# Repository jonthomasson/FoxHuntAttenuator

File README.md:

# FoxHuntAttenuator
Adjustable Pi Attenuator network that aids in ham radio fox hunting.

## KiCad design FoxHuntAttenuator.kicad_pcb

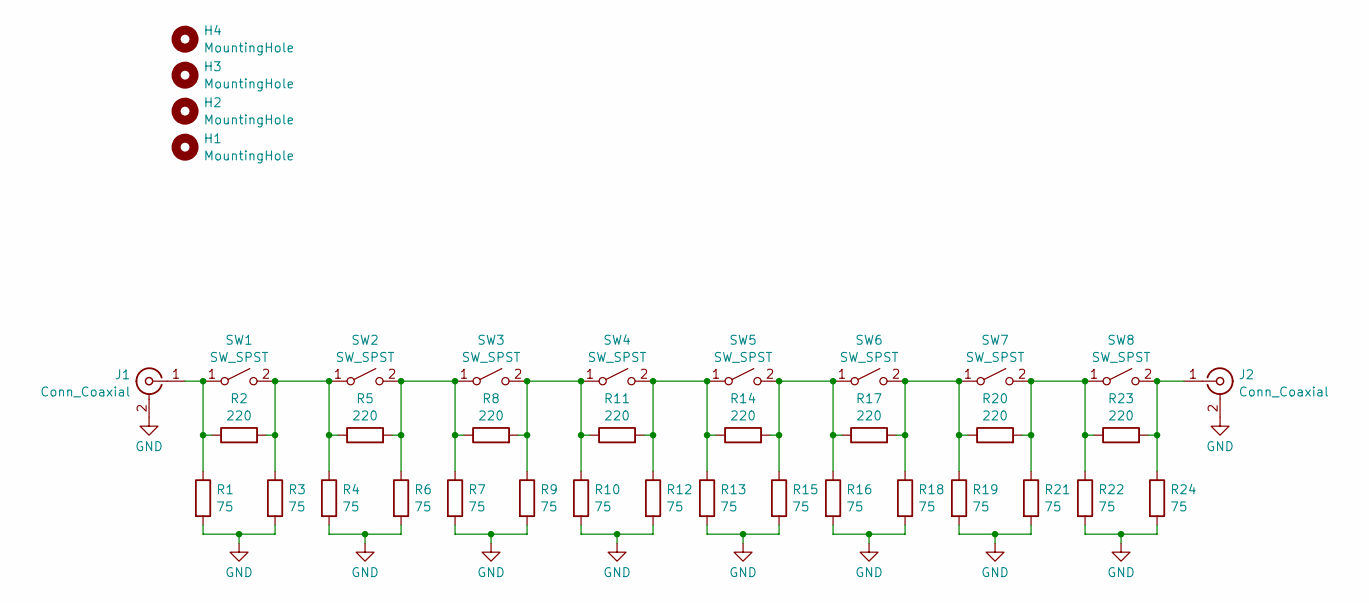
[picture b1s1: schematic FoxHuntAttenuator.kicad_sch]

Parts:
H1, H2, H3, H4: MountingHole; MountingHole_2.7mm_M2.5
J1, J2: Conn_Coaxial; CONBNC002
R1, R3, R4, R6, R7, R9, R10, R12, R13, R15, R16, R18, R19, R21, R22, R24: 75; R_Axial_DIN0309_L9.0mm_D3.2mm_P12.70mm_Horizontal
R2, R5, R8, R11, R14, R17, R20, R23: 220; R_Axial_DIN0309_L9.0mm_D3.2mm_P12.70mm_Horizontal
SW1, SW2, SW3, SW4, SW5, SW6, SW7, SW8: SW_SPST; SWT3

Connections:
GND: J1.2 (Ext), J2.2 (Ext), R1.2, R3.2, R4.2, R6.2, R7.2, R9.2, R10.2, R12.2, R13.2, R15.2, R16.2, R18.2, R19.2, R21.2, R22.2, R24.2
unnamed: J1.1 (In), R1.1, R2.1, SW1.1 (A)
unnamed: J2.1 (In), R23.2, R24.1, SW8.2 (B)
unnamed: R2.2, R3.1, R4.1, R5.1, SW1.2 (B), SW2.1 (A)
unnamed: R5.2, R6.1, R7.1, R8.1, SW2.2 (B), SW3.1 (A)
unnamed: R8.2, R9.1, R10.1, R11.1, SW3.2 (B), SW4.1 (A)
unnamed: R11.2, R12.1, R13.1, R14.1, SW4.2 (B), SW5.1 (A)
unnamed: R14.2, R15.1, R16.1, R17.1, SW5.2 (B), SW6.1 (A)
unnamed: R17.2, R18.1, R19.1, R20.1, SW6.2 (B), SW7.1 (A)
unnamed: R20.2, R21.1, R22.1, R23.1, SW7.2 (B), SW8.1 (A)

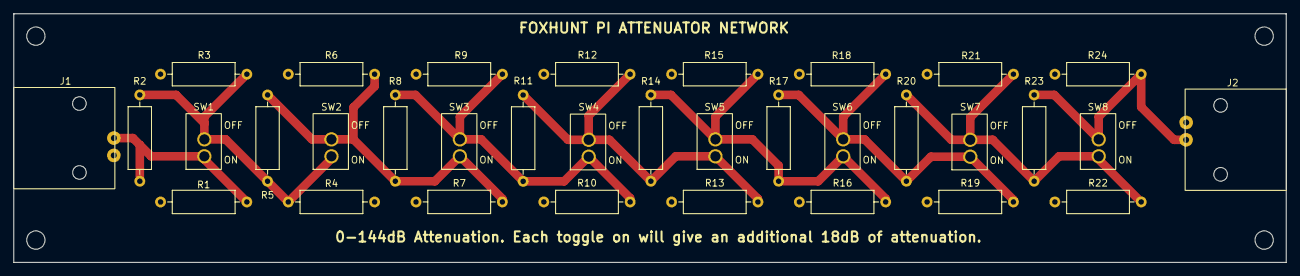
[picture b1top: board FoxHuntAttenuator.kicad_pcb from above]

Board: 2 copper layers, 187.2 x 36.6 mm, 38 parts (0 on the bottom side), 10 nets.

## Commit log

2024-11-24 working on pcb
2024-11-25 pcb layout
2024-11-25 pcb routing
2025-01-03 updating pcb
2025-03-02 updating to kicad 9
2025-03-18 schematic updates
2025-04-13 finishing pcb layout
2025-08-17 adding gerbers
